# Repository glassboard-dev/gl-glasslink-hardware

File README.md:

<p align="center">
  <h3 align="center">⚡ Glasslink</h3>
  <p align="center">
    CMSIS-DAP Compatible Debugger & Programmer for ARM M-Cores
  </p>
</p>

<br />

### Development ⚡
The Glasslink hardware is currently developed in the open source ECAD software [KiCAD](https://www.kicad.org/). The board was created using as many of the included component symbols and footprints as possible. Any custom components are located in the ```Glasslink.lib``` and ```Glasslink.pretty``` files. Additional 3D models were also added to the designa and can be found in the ```models``` folder. The KiCAD [Teardrops](https://github.com/stimulu/kicad-teardrops) extension was used to add teardrops to SMD pads and Vias.

### Board Bring-up 🔼
Once you have a physical piece of hardware in hand, you can begin flashing and setting the device up for your use. The Glasslink hardware is intended to run the open-source firmware [DAPLink](https://github.com/ARMmbed/DAPLink/tree/develop) which supports Drag-N-Drop flashing of certain targets, CDC serial port, CMSIS-DAP WinUSB & HID debug channel as well as WebUSB debug channels. The tested Firwmare has been built using the current ```develop``` branch (as of ```12/10/2021```) using the ```GNU Arm Embedded Toolchain 10-2020-q4-major``` toolchain. More information on building standalone firmware or firmware intended for a specific target (utilizing MSC/Drag-N-Drop) - see [here](https://github.com/ARMmbed/DAPLink/tree/develop/docs).

Once you are ready to flash firmware to the DAPLink hardware, you can utilize the built-in NXP USB ROM Bootloader. A fresh piece of hardware should enumerate immediately into the bootloader when the USB is plugged in. Otherwise, you can hold down the ```nRESET``` pushbutton while plugging in the USB. The ROM Bootloader will enumerate as a MSD labeled ```CRP_DISABLED```.

#### Windows
On windows, to flash a piece of Glasslink hardware you can simply drag your compiled firmware onto the storage device found in File Explorer.

#### Linux
On linux, the ```dd``` command is used to write the firmware to your Glasslink hardware
```console
sudo dd if=lpc11u35_if.bin of=/media/user/CRP\ DISABLD/firmware.bin conv=notrunc
```

### Usage 💻
There are two common applications for utilizing the Glasslink debug probe: [PyOCD](https://pyocd.io/) and [OpenOCD](https://openocd.org/). Check the documentation for each on how to connect a probe, flash a target, debug, etc.

#### CDC Serial Port
The Glasslink hardware enumerates not only as a CMSIS-DAP probe, but also as a CDC serial port. This port can be utilized to send UART/serial data from your Target to a connected Host PC. On Windows a new ```COM``` port should enumerate and on Linux a new ```ACM``` port should enumerate when the Glasslink probe is connected.

To connect the Glasslink serial lines to your targets UART, please reference the 10pin ARM header pinout below. The current design assumes that you are creating your target hardware and have the ability to route your UART pins to the "unused" pins of the SWD header.

**```NOTE - The UART switching for TX<->RX and RX<->TX is done for you on the Glasslink hardware. The target TX pin sould go to pin 9 of the 10pin ARM header.```**

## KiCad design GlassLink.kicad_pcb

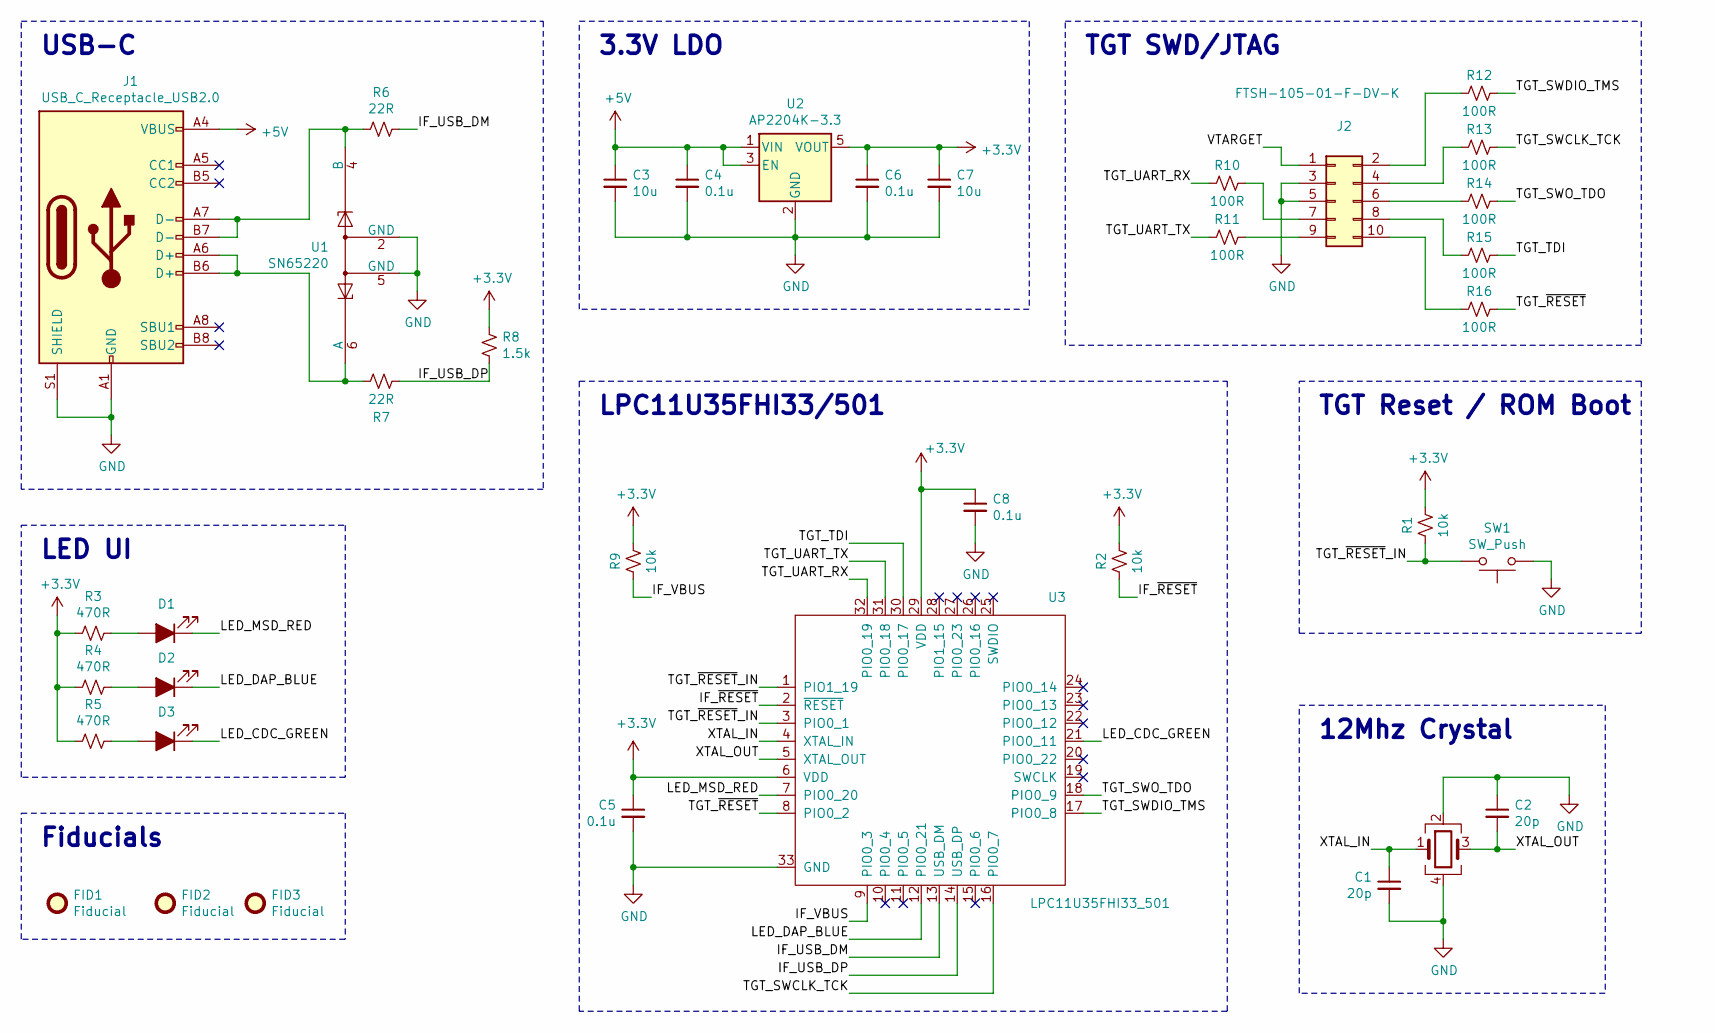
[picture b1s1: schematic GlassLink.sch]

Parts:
C1, C2: 20p; C_0402_1005Metric
C3, C7: 10u; C_0402_1005Metric
C4, C5, C6, C8: 0.1u; C_0402_1005Metric
D1: RED; LED_0603_1608Metric
D2: BLUE; LED_0603_1608Metric
D3: GREEN; LED_0603_1608Metric
FID1, FID2, FID3: Fiducial; Fiducial_0.5mm_Mask1mm
J1: USB_C_Receptacle_USB2.0; USB_C_Receptacle_GCT_USB4085
J2: FTSH-105-01-F-DV-K; PinHeader_2x05_P1.27mm_Vertical_SMD
R1, R2, R9: 10k; R_0402_1005Metric
R3, R4, R5: 470R; R_0402_1005Metric
R6, R7: 22R; R_0402_1005Metric
R8: 1.5k; R_0402_1005Metric
R10, R11, R12, R13, R14, R15, R16: 100R; R_0402_1005Metric
SW1: SW_Push; Panasonic_EVQPUL_EVQPUC
U1: SN65220; SOT-23-6
U2: AP2204K-3.3; SOT-23-5
U3: LPC11U35FHI33_501; QFN-32_EP_6.2x6.2_Pitch0.5mm
Y1: ECS-120-20-30B-TR; Crystal_SMD_5032-4Pin_5.0x3.2mm

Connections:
+3V3: C5.1, C6.1, C7.1, C8.1, R1.1, R2.1, R3.2, R4.2, R5.2, R8.1, R9.1, U2.5 (VOUT), U3.6 (VDD), U3.29 (VDD)
+5V: C3.1, C4.1, J1.A4 (VBUS), J1.A9 (VBUS), J1.B4 (VBUS), J1.B9 (VBUS), U2.1 (VIN), U2.3 (EN)
/IF_USB_DM: R6.1, U3.13 (USB_DM)
/IF_USB_DP: R7.2, R8.2, U3.14 (USB_DP)
/IF_VBUS: R9.2, U3.9 (PIO0_3)
/IF_~RESET: R2.2, U3.2 (~RESET)
/LED_CDC_GREEN: D3.1 (K), U3.21 (PIO0_11)
/LED_DAP_BLUE: D2.1 (K), U3.12 (PIO0_21)
/LED_MSD_RED: D1.1 (K), U3.7 (PIO0_20)
/TGT_SWCLK_TCK: R13.1, U3.16 (PIO0_7)
/TGT_SWDIO_TMS: R12.1, U3.17 (PIO0_8)
/TGT_SWO_TDO: R14.1, U3.18 (PIO0_9)
/TGT_TDI: R15.1, U3.30 (PIO0_17)
/TGT_UART_RX: R10.2, U3.32 (PIO0_19)
/TGT_UART_TX: R11.2, U3.31 (PIO0_18)
/TGT_~RESET: R16.1, U3.8 (PIO0_2)
/TGT_~RESET~_IN: R1.2, SW1.2, U3.1 (PIO1_19), U3.3 (PIO0_1)
/VTARGET: J2.1
/XTAL_IN: C1.1, U3.4 (XTAL_IN), Y1.1
/XTAL_OUT: C2.2, U3.5 (XTAL_OUT), Y1.3
GND: C1.2, C2.1, C3.2, C4.2, C5.2, C6.2, C7.2, C8.2, J1.A1 (GND), J1.A12 (GND), J1.B1 (GND), J1.B12 (GND), J1.S1 (SHIELD), J2.3, J2.5, SW1.1, U1.2 (GND), U1.5 (GND), U2.2 (GND), U3.33 (GND), Y1.2, Y1.4
unnamed: D1.2 (A), R3.1
unnamed: D2.2 (A), R4.1
unnamed: D3.2 (A), R5.1
unnamed: J1.A6 (D+), J1.B6 (D+), R7.1, U1.6 (A)
unnamed: J1.A7 (D-), J1.B7 (D-), R6.2, U1.4 (B)
unnamed: J2.2, R12.2
unnamed: J2.4, R13.2
unnamed: J2.6, R14.2
unnamed: J2.7, R10.1
unnamed: J2.8, R15.2
unnamed: J2.9, R11.1
unnamed: J2.10, R16.2

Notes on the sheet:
USB-C
3.3V LDO
TGT SWD/JTAG
LED UI
LPC11U35FHI33/501
12Mhz Crystal
TGT Reset / ROM Boot
Fiducials

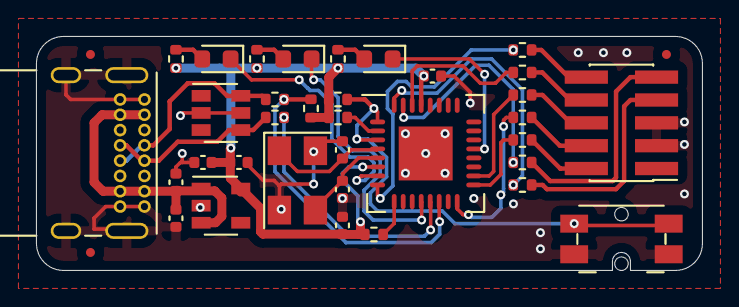
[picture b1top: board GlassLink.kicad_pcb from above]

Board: 2 copper layers, 37.0 x 13.0 mm, 37 parts (0 on the bottom side), 32 nets.

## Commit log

2020-12-08 First commit of project files.
2020-12-08 Adding gitignore for Preview Files
2020-12-08 Committing .gitignore again..
2020-12-08 Updating .gitignore again.. again..
2020-12-08 Removing __Previews folder
2020-12-10 WIP: Components placed
    Awaiting track layout.
2020-12-10 WIP: Layout finished
    In review
2020-12-10 WIP: Added Type C Connector
2020-12-11 WIP: Clean DRC
2020-12-11 Removing History folder aftering being added to .gitignore
2020-12-12 WIP: Updating Glassboard G Logo schematic symbol
2020-12-14 Submitting files ordered w/ PCBWay
2021-01-18 Updating for R0.2
    Updated test point position, added pull up on D+ line, and updated GlassLink net
2021-01-19 Clean DRC - Removing project outputs
2021-01-19 Cleaning up ignored files
2021-01-19 Order submitted to PCBWay for R0.2
2021-01-19 Removing unused schematic sheets
2021-01-27 Fixing missing G logo on bottom solder mask :(
2021-02-25 Set CN1 to DNP and updated the outjob to support 3d-step exports
2021-04-22 Changed micro for the LPC11U35
2021-05-20 Replaced the 401 variant of the LPC11U35 for the 501 with 2k more SRAM
2021-12-09 Adding KiCAD design files for the GlassLink R0.5
2021-12-09 Pull TGT Reset to the TGT VCC instead of the prog VCC
2021-12-10 Adding Glassboard G logo
2021-12-10 Adding a README and LICENSE
2021-12-13 Fixing dd command for flashing DAPLink firmware
2022-01-12 Pulling TGT_RESET to DAPLink 3.3V rail
2022-01-20 Fixing trace on top layer behind Glasslabs label

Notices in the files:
README.md:
License: CC BY 4.0
